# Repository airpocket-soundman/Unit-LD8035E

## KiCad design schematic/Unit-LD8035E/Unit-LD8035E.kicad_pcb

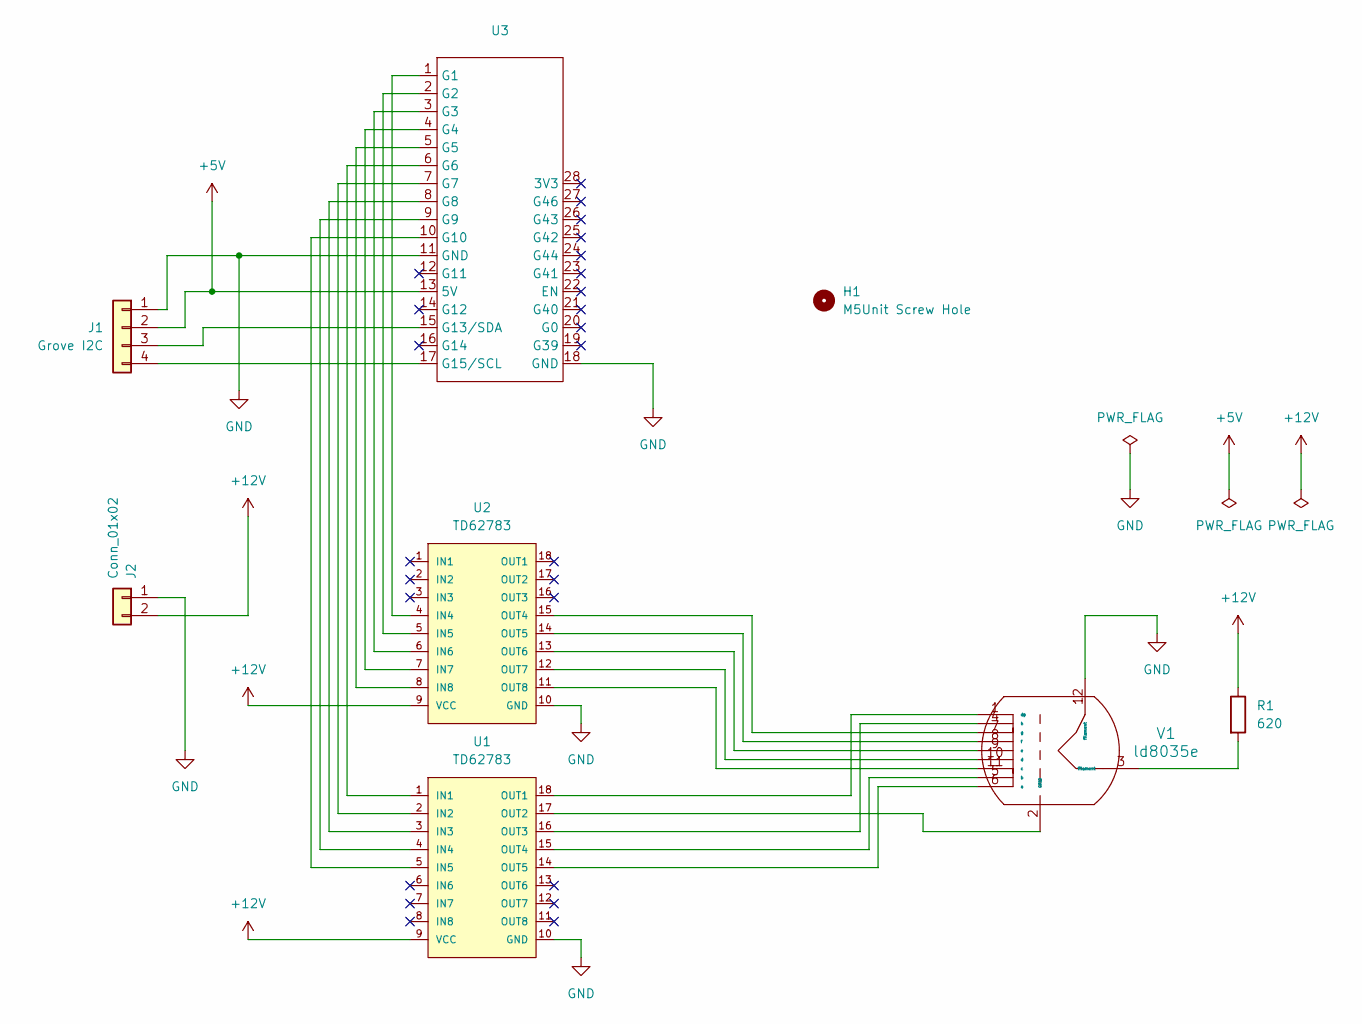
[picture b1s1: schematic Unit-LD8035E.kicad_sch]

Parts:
H1: M5Unit Screw Hole; unit_mounting_hole
J1: Grove I2C; HY2.0-4P
J2: Conn_01x02; JST_XH_B2B-XH-A_1x02_P2.50mm_Vertical
R1: 620; R_Axial_DIN0207_L6.3mm_D2.5mm_P7.62mm_Horizontal
U1, U2: TD62783; SOP-18_7x12.5mm_P1.27mm
U3: M5StampS3
V1: ld8035e; LD8035E

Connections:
+5V: J1.2, U3.13 (5V)
+12V: J2.2, R1.1, U1.9 (VCC), U2.9 (VCC)
GND: J1.1, J2.1, U1.10 (GND), U2.10 (GND), U3.11 (GND), U3.18 (GND), V1.12 (filament)
unnamed: J1.3, U3.15 (G13/SDA)
unnamed: J1.4, U3.17 (G15/SCL)
unnamed: R1.2, V1.3 (filament)
unnamed: U1.1 (IN1), U3.6 (G6)
unnamed: U1.2 (IN2), U3.7 (G7)
unnamed: U1.3 (IN3), U3.8 (G8)
unnamed: U1.4 (IN4), U3.9 (G9)
unnamed: U1.5 (IN5), U3.10 (G10)
unnamed: U1.18 (OUT1), V1.1 (dp)
unnamed: U1.17 (OUT2), V1.2 (GRID)
unnamed: U1.16 (OUT3), V1.4 (h)
unnamed: U1.15 (OUT4), V1.5 (b)
unnamed: U1.14 (OUT5), V1.6 (a)
unnamed: U2.4 (IN4), U3.1 (G1)
unnamed: U2.5 (IN5), U3.2 (G2)
unnamed: U2.6 (IN6), U3.3 (G3)
unnamed: U2.7 (IN7), U3.4 (G4)
unnamed: U2.8 (IN8), U3.5 (G5)
unnamed: U2.15 (OUT4), V1.7 (g)
unnamed: U2.14 (OUT5), V1.8 (f)
unnamed: U2.13 (OUT6), V1.9 (e)
unnamed: U2.12 (OUT7), V1.10 (d)
unnamed: U2.11 (OUT8), V1.11 (c)

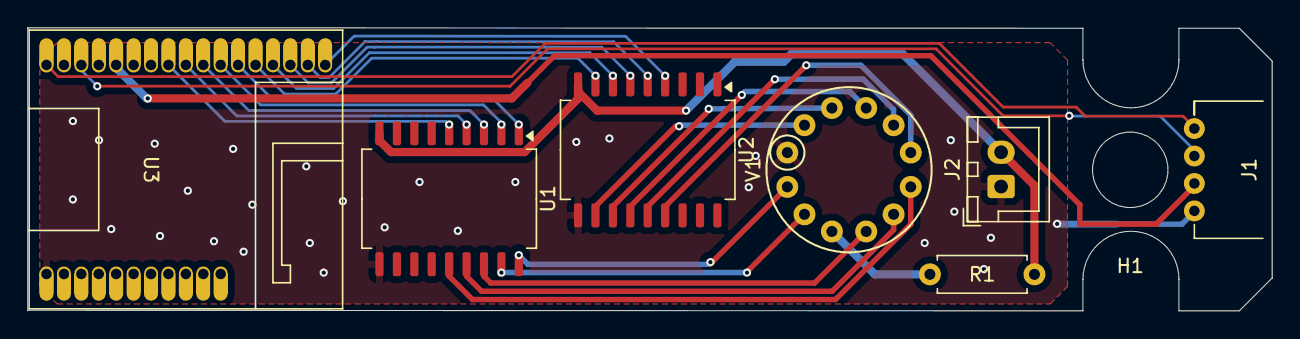
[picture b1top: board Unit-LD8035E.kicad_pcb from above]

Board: 2 copper layers, 90.7 x 20.6 mm, 8 parts (0 on the bottom side), 26 nets.

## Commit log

2024-07-12 schematic
2024-07-18 回路修正
2024-07-20 コード制作開始
2024-07-21 code
2024-07-23 いろいろ
2024-07-23 ループデモ追加
